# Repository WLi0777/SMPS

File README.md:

# SMPS
SMPS (Switch mode power supply) based on the two-switch converter

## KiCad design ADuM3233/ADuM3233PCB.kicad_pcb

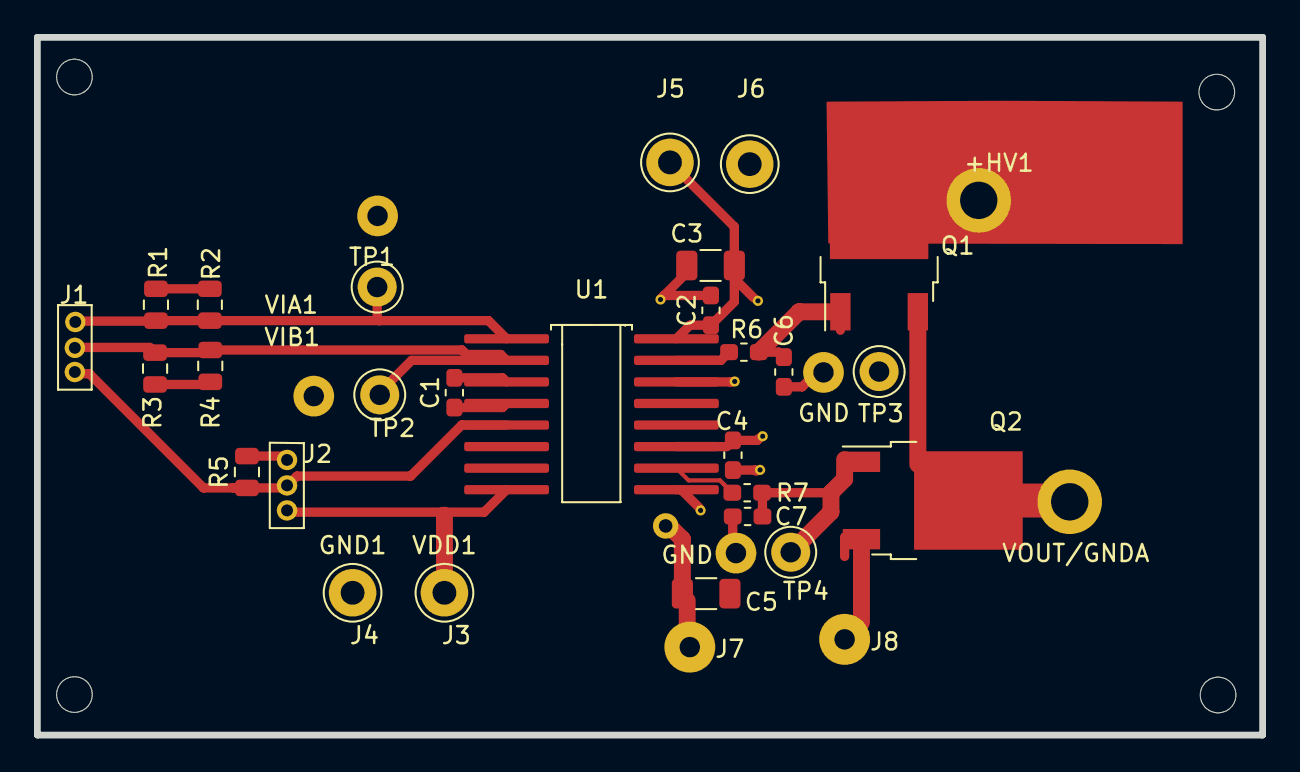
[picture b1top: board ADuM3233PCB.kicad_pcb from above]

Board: 2 copper layers, 72.2 x 41.1 mm, 29 parts (0 on the bottom side), 8 nets.

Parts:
+HV1: IN; MountingHole_2.2mm_M2_ISO14580_Pad
C1, C2, C4: 1uF; C_0603_1608Metric_Pad1.05x0.95mm_HandSolder
C3, C5: 10uF; C_1206_3216Metric
C6, C7: 2.2nF; C_0603_1608Metric_Pad1.05x0.95mm_HandSolder
J3: VDD1; TestPoint_Loop_D2.60mm_Drill1.4mm_Beaded
J4: GND1; TestPoint_Loop_D2.60mm_Drill1.4mm_Beaded
J5: VDDA; TestPoint_Loop_D2.60mm_Drill1.4mm_Beaded
J6: VOUT/GNDA; TestPoint_Loop_D2.60mm_Drill1.4mm_Beaded
J7: VDDB; TestPoint_Loop_D2.60mm_Drill1.4mm_Beaded
J8: GNDB; TestPoint_Loop_D2.60mm_Drill1.4mm_Beaded
Q1, Q2: DNI; TO-252-2
R1, R2, R3, R4: 100; R_0805_2012Metric
R5: 10k; R_0805_2012Metric
R6, R7: 0; R_0603_1608Metric_Pad1.05x0.95mm_HandSolder
TP1: VIA1; TestPoint_Loop_D2.60mm_Drill1.4mm_Beaded
TP2: V1B1; TestPoint_Loop_D2.60mm_Drill1.4mm_Beaded
TP3, TP4: Conn_01x02; TestPoint_Loop_D2.60mm_Drill1.4mm_Beaded
U1: ADUM3223BRZ-RL7; SOIC-16_4.55x10.3mm_P1.27mm
VOUT/GNDA: Conn_01x01; MountingHole_2.2mm_M2_ISO14580_Pad

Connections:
/DISABLE: R5.1, U1.5
/V0B: C7.2, Q2.1, R7.2, TP4.1
/VDA: C6.2, Q1.1, R6.1, TP3.1
/VIA1: R1.1, R2.1, TP1.1, U1.1
/VIB1: R3.2, R4.2, TP2.1, U1.2
GND: C1.1, C1.2, C2.1, C2.2, C3.1, C3.2, C4.1, C4.2, C5.1, C6.1, C7.1, J3.1, J4.1, J5.1, J7.1, J8.1, Q1.3, Q2.3, R1.2, R2.2, R3.1, R4.1, R5.2, U1.3, U1.4, U1.8, U1.9, U1.11, U1.14, U1.16, VOUT/GNDA.1
unnamed: R6.2, U1.15
unnamed: R7.1, U1.10

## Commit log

2023-05-03 Create d
